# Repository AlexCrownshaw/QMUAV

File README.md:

# QMUAV
The Quad-Motor UAV is a platform designed to allow for learning of Guidance, Navigation and Control of autonomous systems.

## Aims
The Main aim of the QMUAV project is to build an autonomously hovering Quadcopter using ‘off the self-consumer hardware’ and a uniquely design Flight Control System (FCS). The purpose of this being to develop and learn skills in the GNC or Guidance Navigation and Control sector of Aerospace engineering. The project also allows for the demonstration of key engineering skills including the use of technical software (MATLAB – SIMULINK/SOLIDWORKS CAD/Autodesk EAGLE CAD), software engineering in a predominately C++ based language and using Current engineering knowledge to develop a system and make valid design choices.

## Documentation
The latest version of the documentation can be found as a Word document stored in the repository.

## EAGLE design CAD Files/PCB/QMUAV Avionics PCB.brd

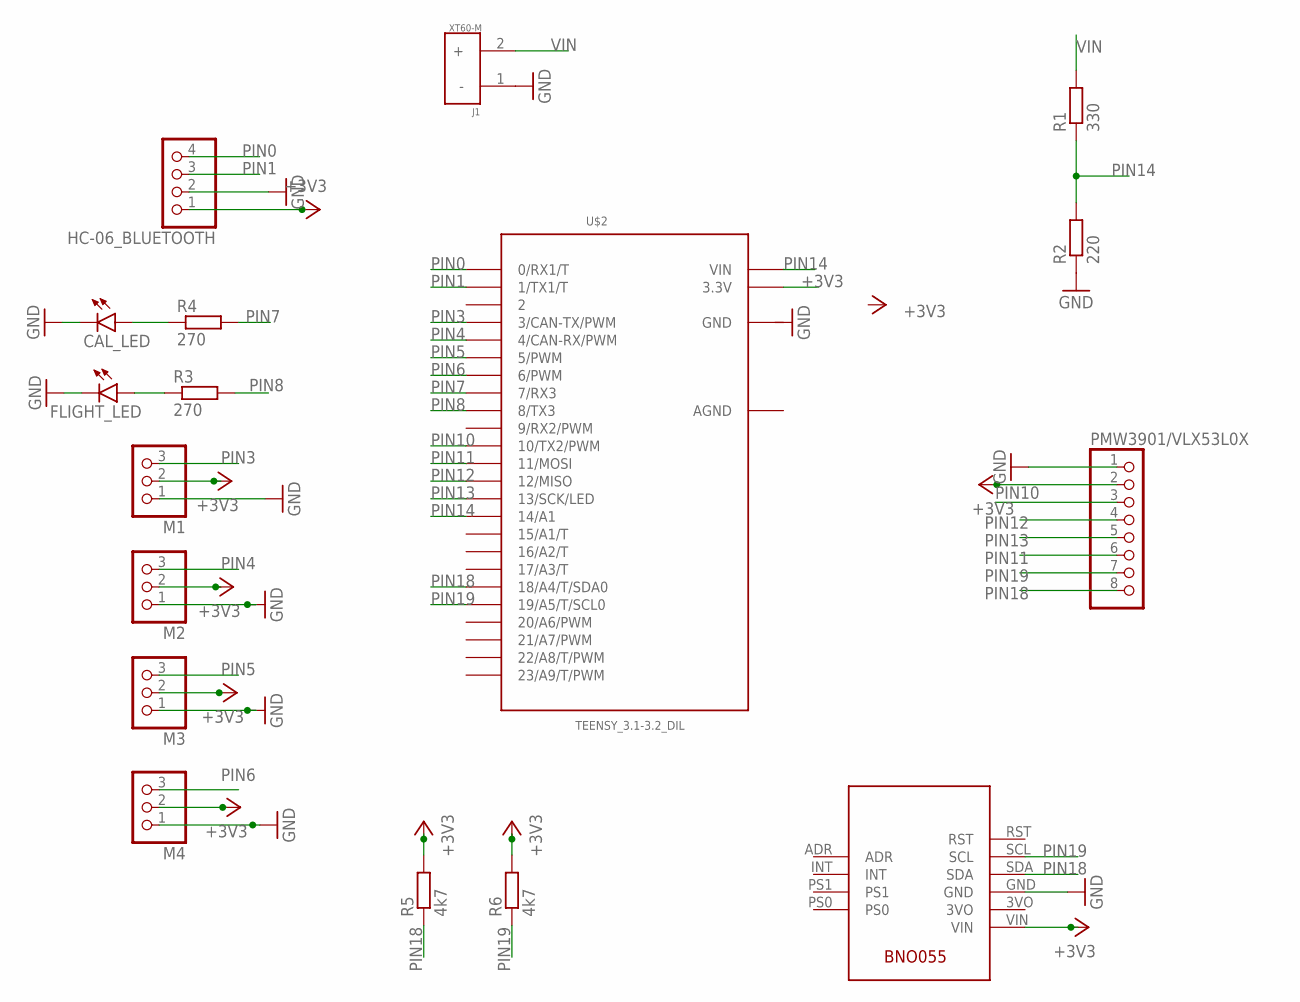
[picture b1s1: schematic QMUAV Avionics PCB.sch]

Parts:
CAL_LED: LED5MM
FLIGHT_LED: LED5MM
HC-06_BLUETOOTH: PINHD-1X4; 1X04
J1: XT60-M; AMASS_XT60-M
M1, M2, M3, M4: PINHD-1X3; 1X03
PMW3901/VLX53L0X: PINHD-1X8; 1X08
R1: 330; 0207/10
R2: 220; 0207/10
R3, R4: 270; 0207/10
R5, R6: 4k7; 0207/10
U$2: TEENSY_3.1-3.2_DIL; TEENSY_3.0-3.2&LC_DIL
U$3: BNO055

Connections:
+3V3: HC-06_BLUETOOTH.1, M1.2, M2.2, M3.2, M4.2, PMW3901/VLX53L0X.2, R5.2, R6.2, U$2.3.3V, U$3.VIN
AGND: U$2.AGND
GND: CAL_LED.K (C), FLIGHT_LED.K (C), HC-06_BLUETOOTH.2, J1.1 (-), M1.1, M2.1, M3.1, M4.1, PMW3901/VLX53L0X.1, R2.1, U$2.GND, U$3.GND
unnamed: CAL_LED.A, R4.1
unnamed: FLIGHT_LED.A, R3.1
PIN0: HC-06_BLUETOOTH.4, U$2.0 (0/RX1/T)
PIN1: HC-06_BLUETOOTH.3, U$2.1 (1/TX1/T)
PIN3: M1.3, U$2.3 (3/CAN-TX/PWM)
PIN4: M2.3, U$2.4 (4/CAN-RX/PWM)
PIN5: M3.3, U$2.5 (5/PWM)
PIN6: M4.3, U$2.6 (6/PWM)
PIN7: R4.2, U$2.7 (7/RX3)
PIN8: R3.2, U$2.8 (8/TX3)
PIN10: PMW3901/VLX53L0X.3, U$2.10 (10/TX2/PWM)
PIN11: PMW3901/VLX53L0X.6, U$2.11 (11/MOSI)
PIN12: PMW3901/VLX53L0X.4, U$2.12 (12/MISO)
PIN13: PMW3901/VLX53L0X.5, U$2.13 (13/SCK/LED)
PIN14: R1.1, R2.2, U$2.14/A0 (14/A1), U$2.VIN
PIN18: PMW3901/VLX53L0X.8, R5.1, U$2.18/A4 (18/A4/T/SDA0), U$3.SDA
PIN19: PMW3901/VLX53L0X.7, R6.1, U$2.19/A5 (19/A5/T/SCL0), U$3.SCL
VIN: J1.2 (+), R1.2

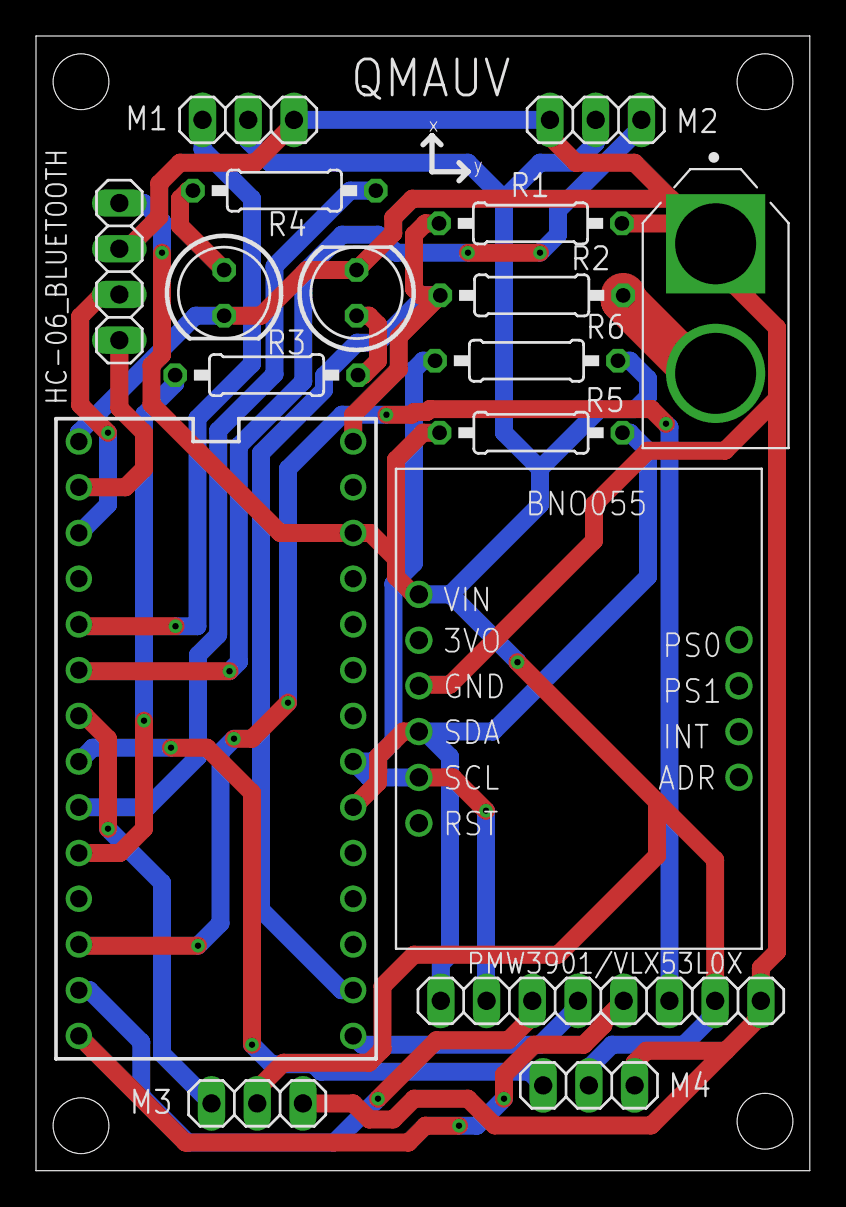
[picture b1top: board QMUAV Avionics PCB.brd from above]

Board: 2 copper layers, 43.0 x 63.0 mm, 17 parts (0 on the bottom side), 20 nets.

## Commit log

2020-09-24 Adds Documentation Word document
2020-09-24 Adds SIMULINK Simulation Model
2020-09-24 FCS v0.1
2020-09-24 Creates "Simulation" Folder
2020-09-24 Adds "CAD" Folder
2020-09-24 Fixed Bad Upload
2020-09-25 Includes Libraries
2020-10-22 Updated Documentation
